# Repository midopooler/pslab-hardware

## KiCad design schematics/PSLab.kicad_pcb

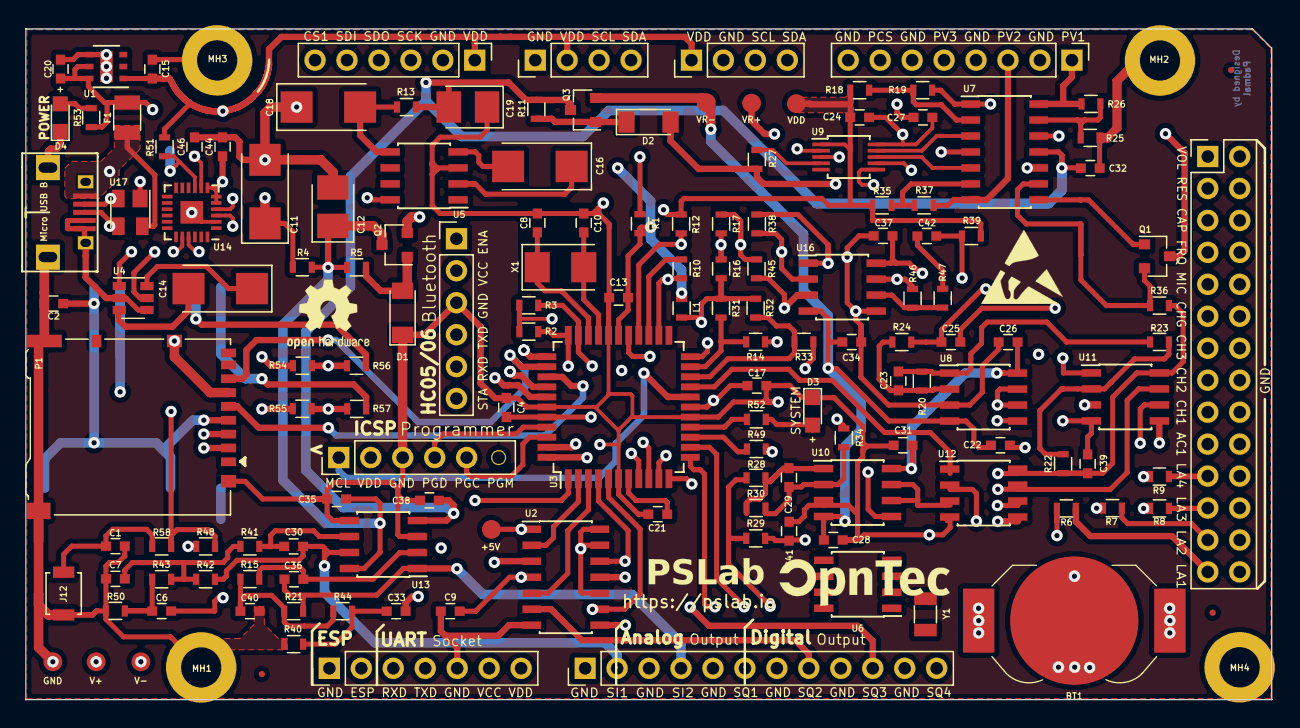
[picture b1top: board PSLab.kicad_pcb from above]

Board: 4 copper layers, 99.0 x 53.3 mm, 171 parts (0 on the bottom side), 118 nets.

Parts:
BT1: 1225; BatteryHolder_LINX_BAT-HLD-012-SMT
C1, C30, C36: 1nF; C_0603
C2, C4, C9, C13, C17, C22, C24, C25, C26, C27, C28, C31, C32, C34, C35, C37, C38, C39, C41: 0.1u; C_0603
C6, C15, C21, C33: 10u; C_0603
C7, C40: 10nF; C_0603
C8, C10: 33p; C_0603
C11, C14, C16, C18: 100u; CP_Tantalum_Case-C_EIA-6032-28_Reflow
C12, C19: 33u; CP_Tantalum_Case-B_EIA-3528-21_Reflow
C20, C42: 1u; C_0603
C23, C29: 3p3; C_0603
C44, C46: 4.7u; C_0603
CON1: USB-MINI-B; USB_Micro-B
D1, D2: 6V8; D_MiniMELF
D3, D4: LED; LED_0805
F1: 0.5A; Fuse_SMD1206_Reflow
J1: Programmer; Pin_Header_Straight_1x06_Pitch2.54mm
J2: DoublePins; Pin_Header_Straight_2x14_Pitch2.54mm
J4: Outputs; Pin_Header_Straight_1x12_Pitch2.54mm
J5: Bluetooth; Pin_Header_Straight_1x06_Pitch2.54mm
J6: I2C-1; Pin_Header_Straight_1x04_Pitch2.54mm
J7: UART/ESP; Pin_Header_Straight_1x07_Pitch2.54mm
J8: Power Pins; Pin_Header_Straight_1x08_Pitch2.54mm
J9: SPI; Pin_Header_Straight_1x06_Pitch2.54mm
J10: GND; Measurement_Point_Square-SMD-Pad_Small
J11: Vbus; Measurement_Point_Square-SMD-Pad_Small
J12: SD_Switch; SW_SPST_B3U-1000P
J13: D+; Measurement_Point_Square-SMD-Pad_Small
J14: D-; Measurement_Point_Square-SMD-Pad_Small
J16: I2C-2; Pin_Header_Straight_1x04_Pitch2.54mm
JP1: ESP Reset; GS2
JP2: UART Reset; GS2
L1: 10uH; L_0603
MH1, MH2, MH3, MH4: M; MountingHole_3.2mm_M3_DIN965_Pad
P1: SDCard; microSD_HC_Hirose_DM3AT-SF-PEJM5
Q1, Q3: MMBT3906; SOT-23
Q2: MMBT3904; SOT-23
R1, R2, R3, R10, R14, R16, R17, R18, R19, R21, R22, R23, R25, R28, R29, R31, R32, R33, R35, R37, R38, R39, R42: 10K; R_0603
R4, R13, R54, R55, R56, R57: 18; R_0603
R5, R11, R27, R36, R47, R51: 1K; R_0603
R6, R7, R8, R9, R49, R58: 200; R_0603
R12, R15, R26, R41, R43, R44, R48, R52, R53: 5K1; R_0603
R20, R30, R40, R46, R50: 200K; R_0603
R24, R34, R45: 1M; R_0603
S1: OpenHardware; OSHW-Logo2_7.3x6mm_SilkScreen
S2: PSLab_Logo
S3: ESD-Logo; ESD-Logo_6.6x6mm_SilkScreen
S5, S8: OpnTec_Logo
S6: FOSSASIA_Logo_S; FOSSASIA_Logo
S7: PSL_Logo
S9: QR_Code; Website_QR
S10: FOSSASIA_Logo_L; FOSSASIA_LogoL
TP1, TP2, TP3, TP4, TP8, TP9, TP10: TEST; Measurement_Point_Round-SMD-Pad_Small
TP5, TP6, TP7: Fiducial; Fiducial_0.5mm_Dia_1mm_Outer
TP11: CR1225; Battery_CR1225
U1: LDFM33PVR; DFN-6-1EP_3x3mm_Pitch0.95mm
U2: 74HC126; SOIC-14_3.9x8.7mm_Pitch1.27mm
U3: PIC24EP256GP204; TQFP-44_10x10mm_Pitch0.8mm
U4: TC1240A; SOT-23-6
U5: 7660; SOIC-8_3.9x4.9mm_Pitch1.27mm
U6: DS1307Z+; SOIC-8_3.9x4.9mm_P1.27mm
U7: LM324; SOIC-14_3.9x8.7mm_Pitch1.27mm
U8, U10, U13, U16: TL082; SOIC-8_3.9x4.9mm_Pitch1.27mm
U9: MCP4728; MSOP-10_3x3mm_Pitch0.5mm
U11, U12: 6S21; SOIC-8_3.9x4.9mm_Pitch1.27mm
U14: CP2102; QFN-24-1EP_4x4mm_Pitch0.5mm
U15: ESP8266; Hopref_RFM9XW_SMD
U17: SP0503BAHT; SOT-143
X1: 12MHz; Crystal_SMD_5032-2pin_5.0x3.2mm
Y1: 32.768 kHz; Crystal_SMD_3215-2Pin_3.2x1.5mm

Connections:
3.3V: C2.2, C4.1, C13.2, C15.2, C44.1, J1.2, J6.2, J7.7, J9.1, J16.1, L1.2, P1.4, R1.1, R2.2, R3.2, R48.1, R51.2, U1.1, U3.28, U3.40, U14.5, U14.6, U14.7, U15.3, U15.8, U15.11
+5V: C9.2, C20.2, F1.2, J5.2, J7.6, R53.2, TP3.1, U1.5, U1.6, U2.1, U2.4, U2.10, U2.13, U2.14, U4.1, U6.8
/ERxD: R56.1, U15.15
/ESPROG: J7.2, U15.12
/ETxD: R57.1, U15.16
/I/O Processing/DAC1: U7.3, U9.9
/I/O Processing/DAC2: U7.5, U9.8
/I/O Processing/DAC4: U7.10, U9.6
/ID1: R6.2, U3.8
/ID2: R7.2, U3.9
/ID3: R8.2, U3.10
/ID4: R9.2, U3.11
/MRxD: R54.2, U14.20
/MTxD: R55.2, U14.21
ACH1: C25.2, J2.19
AN8: J2.1, U3.27
AVdd: C17.2, C24.2, C39.2, C41.2, L1.1, R12.1, R16.2, R18.1, R22.2, R29.1, R31.2, R32.2, R35.1, R36.1, R39.2, TP8.1, U3.17, U9.1, U11.8, U12.8
CAP: J2.5, R10.1, U3.24
CH1: C25.1, J2.17, R24.1
CH1out: U3.22, U11.1
CH2: J2.15, R34.1
CH2out: U3.19, U12.1
CH3: J2.13, R45.2, U16.3
CH3.GAIN: J2.11, R38.1, U16.2
CH3out: R32.1, R33.1, U3.20
CS: J9.6, U3.37
CS.CH1: U3.12, U11.5
CS.CH2: U3.13, U12.5
CS.CH3: P1.2, U3.1
D+: CON1.3, J13.1, U14.3, U17.3
D-: CON1.2, J14.1, U14.4, U17.2
FCin: J2.7, R49.2
GND: BT1.2, C1.2, C2.1, C4.2, C7.2, C8.1, C9.1, C10.1, C11.2, C12.2, C13.1, C15.1, C17.1, C18.1, C19.1, C20.1, C21.1, C22.1, C24.1, C26.1, C27.2, C28.1, C31.1, C32.2, C34.1, C35.1, C37.1, C38.1, C39.1, C40.2, C41.1, C44.2, C46.2, CON1.4, CON1.5, CON1.6, CON1.7, CON1.8, CON1.9, D1.1, D2.2, D3.1, D4.1, J1.3, J2.2, J2.4, J2.6, J2.8, J2.10, J2.12, J2.14, J2.16, J2.18, J2.20, J2.22, J2.24, J2.26, J2.28, J4.1, J4.3, J4.5, J4.7, J4.9, J4.11, J5.3, J6.1, J7.1, J7.5, J8.2, J8.4, J8.6, J8.8, J9.2, J10.1, J12.1, J16.2, JP1.1, JP2.2, MH1.1, MH2.1, MH3.1, MH4.1, P1.6, P1.11, R17.2, R25.1, R27.2, R40.2, R45.1, R50.2, TP4.1, U1.4, U1.7, U2.7, U3.6, U3.16, U3.29, U3.39, U4.2, U4.4, U5.3, U6.4, U8.3, U9.10, U10.3, U11.4, U12.4, U13.3, U13.5, U14.2, U14.25, U15.9, U15.10, U16.5, U17.1
IDA: J2.27, R6.1
IDB: J2.25, R7.1
IDC: J2.23, R8.1
IDD: J2.21, R9.1
MCLR: J1.1, R1.2, U3.18
MIC: C42.2, J2.9, R39.1
MICout: R14.1, R31.1, U3.21
unnamed: BT1.1, U6.3
unnamed: C1.1, J12.2, R58.2
unnamed: C6.2, R43.1, R50.1
unnamed: C7.1, R41.2, R42.1, R43.2
unnamed: C8.2, U3.31, X1.1
unnamed: C10.2, U3.30, X1.2
unnamed: C11.1, R4.2, U4.5, U5.8
unnamed: C14.1, U4.6
unnamed: C14.2, U4.3
unnamed: C16.1, U5.2
unnamed: C16.2, U5.4
unnamed: C18.2, R13.2, U5.5
unnamed: C21.2, U3.7
unnamed: C23.1, R20.1, R23.2, U8.1
unnamed: C23.2, R20.2, R24.2, U8.2
unnamed: C29.1, R28.1, R30.1, U10.1
unnamed: C29.2, R30.2, R34.2, U10.2
unnamed: C30.2, R41.1, U13.6
unnamed: C33.2, R40.1, R44.1
unnamed: C36.2, R15.1, U13.2
unnamed: C40.1, R15.2, R21.2, R44.2
unnamed: C42.1, R47.2
unnamed: D1.2, Q2.1, R5.2
unnamed: D2.1, Q3.1, R11.1
unnamed: D3.2, R52.1
unnamed: D4.2, R53.1
unnamed: JP1.2, U15.1
unnamed: JP2.1, R51.1, U14.9
unnamed: Q1.1, U7.8
unnamed: Q1.2, R36.2, U7.9
unnamed: R10.2, U3.25
unnamed: R14.2, R46.2, U16.7
unnamed: R16.1, R17.1, U8.5, U10.5
unnamed: R18.2, R19.1, U7.2
unnamed: R19.2, U7.1, U7.12
unnamed: R22.1, R23.1, U11.2
unnamed: R25.2, R26.1, U7.13
unnamed: R27.1, U9.4
unnamed: R28.2, R29.2, U12.2
unnamed: R33.2, R38.2, U16.1
unnamed: R35.2, R37.1, U7.6
unnamed: R46.1, R47.1, U16.6
unnamed: R49.1, U3.14
unnamed: U2.2, U3.2
unnamed: U2.5, U3.3
unnamed: U6.1, Y1.1
unnamed: U6.2, Y1.2
unnamed: U10.6, U10.7, U12.3
unnamed: U8.6, U8.7, U11.3
PCS: J8.7, Q1.3
PGC2: J1.5, U3.42
PGD2: J1.4, U3.41
PVS1: J8.1, R26.2, U7.14
PVS2: J8.3, R37.2, U7.7
PVS3: J8.5, U9.7
RP147: R52.2, U3.15
RxD: J5.5, J7.3, R54.1, R56.2, U3.43
SCK: J9.3, P1.5, U3.36, U11.7, U12.7
SCL: J6.3, J16.3, R2.1, U3.33, U6.6, U9.2
SDA: J6.4, J16.4, R3.1, U3.32, U6.5, U9.3
SDI: J9.5, P1.7, U3.35
SDO: J9.4, P1.3, U3.34, U11.6, U12.6
SEN: J2.3, R12.2, U3.26
SINE1: C30.1, J4.2, R42.2, U13.7
SINE2: C36.1, J4.4, R21.1, U13.1
SQ3: C33.1, U2.12, U3.4
SQ4: C6.1, U2.9, U3.5
SQR1: J4.6, U2.3
SQR2: J4.8, U2.6
SQR3: J4.10, U2.11
SQR4: J4.12, U2.8
SW: R48.2, R58.1, U3.38
TxD: J5.4, J7.4, R55.1, R57.2, U3.44
V+: C12.1, C27.1, C35.2, Q2.3, R4.1, R5.1, TP2.1, U7.4, U13.8
V-: C19.2, C32.1, C38.2, Q3.3, R11.2, R13.1, TP1.1, U7.11, U13.4
VBus: C46.1, CON1.1, F1.1, J11.1, U14.8, U17.4
VR+: C26.2, C31.2, C37.2, Q2.2, TP9.1, U8.8, U10.8, U16.8
VR-: C22.2, C28.2, C34.2, Q3.2, TP10.1, U8.4, U10.4, U16.4

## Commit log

2019-04-05 feat: added components for RTC
2019-04-05 route: adding missing routes after importing net
2019-04-05 route: rearrange to get more space
2019-04-05 route: rtc module placement
